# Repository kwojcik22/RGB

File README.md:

# RGB LED Controller Project

This repository contains hardware and firmware for an RGB LED controller based on the STM32F091 microcontroller. The project includes PCB design files, firmware source code, and documentation.

## Project Structure

- **pcb projects/**  
  KiCad PCB design files for the RGB LED controller hardware.
  - `RGBLED_v1/` – Main PCB project files and backups.
  - `doc/` – Additional PCB-related documentation.

- **firmware/W8/**  
  STM32CubeIDE firmware project for the STM32F091 MCU.
  - `Core/` – Main application source and header files.
  - `dimming/` – LED dimming logic.
  - `Drivers/` – HAL and CMSIS drivers.
  - `Debug/`, `Release/` – Build output directories.
  - `STM32F091RCTX_FLASH.ld` – Linker script.
  - `.ioc` – STM32CubeMX configuration file.

- **doc/**  
  Documentation and resources.
 
## Getting Started

### Requirements

- STM32CubeIDE (for firmware development)
- KiCad (for PCB design)
- ST-Link programmer/debugger
- STM32F091-based hardware

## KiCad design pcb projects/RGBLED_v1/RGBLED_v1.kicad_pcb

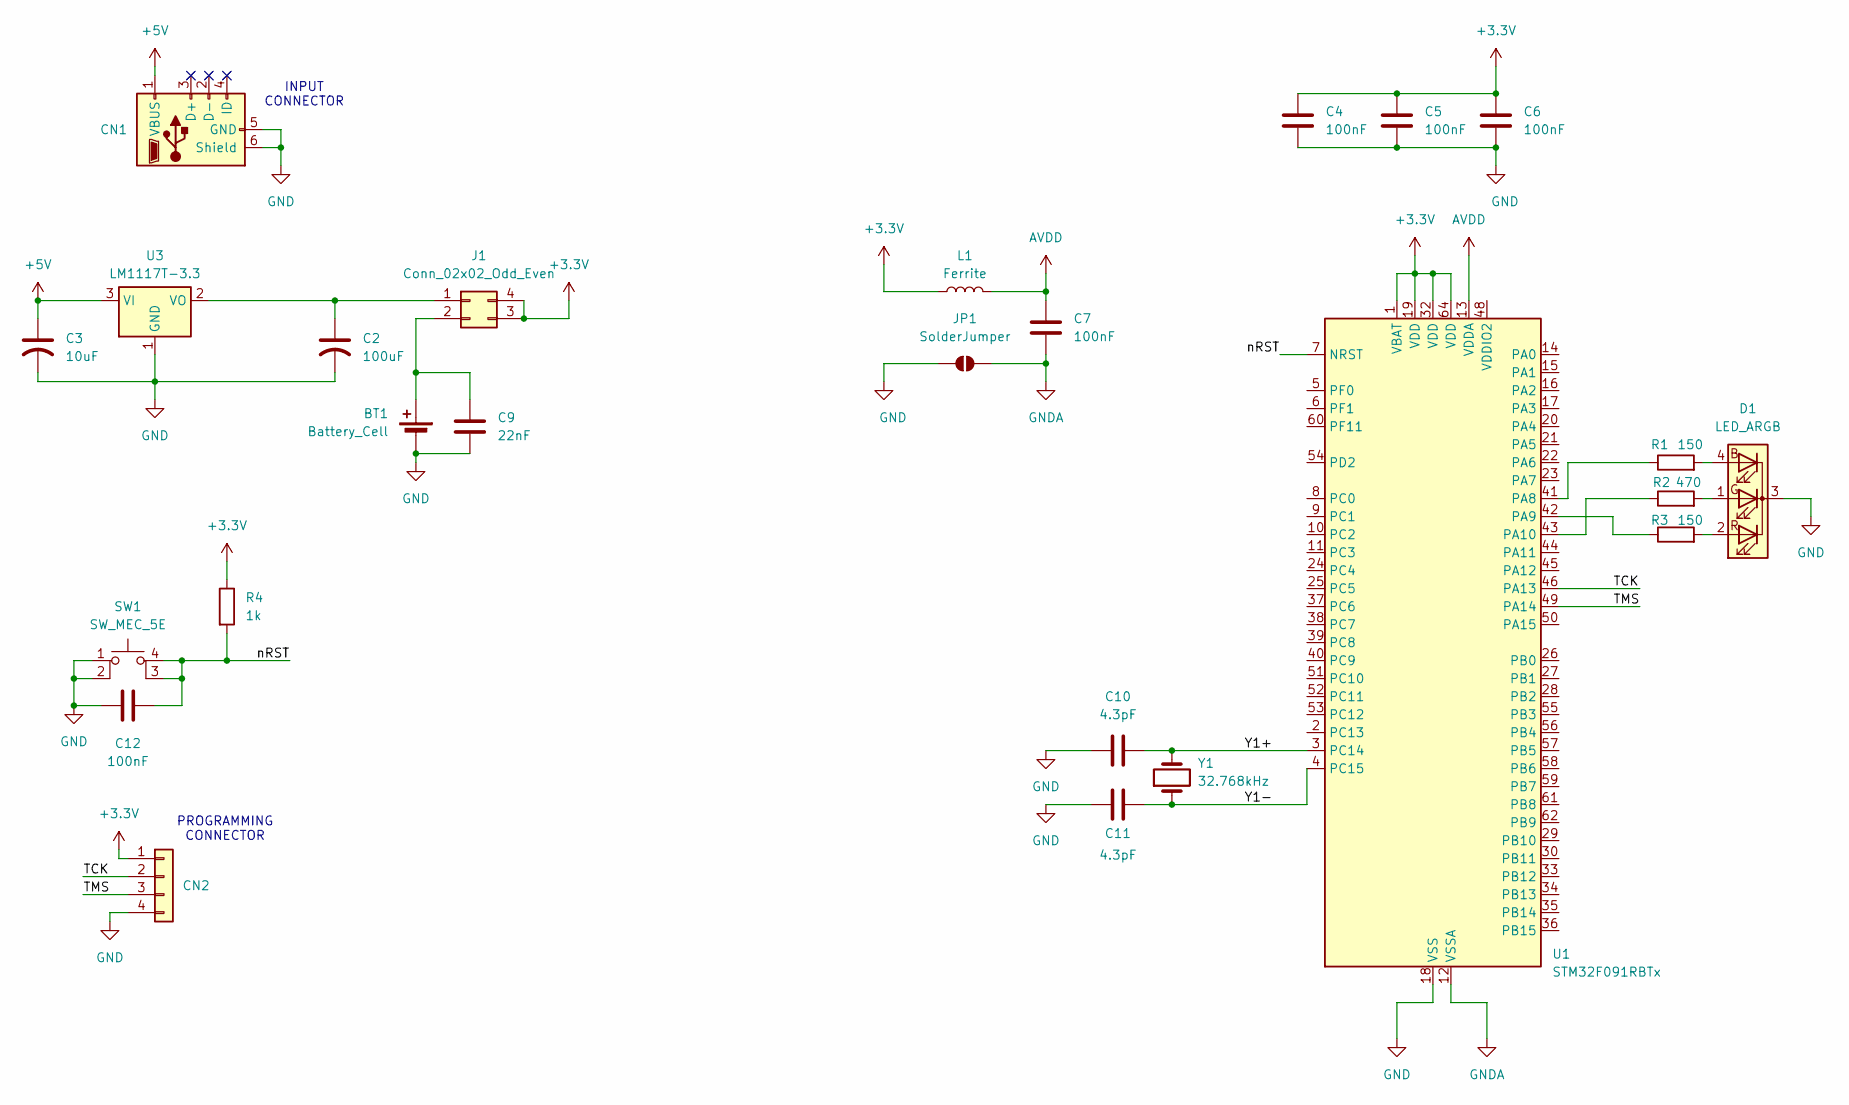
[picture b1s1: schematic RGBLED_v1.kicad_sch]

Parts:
BT1: Battery_Cell; BatteryHolder_MYOUNG_BS-07-A1BJ001_CR2032
C2: 100uF; CP_EIA-3528-21_Kemet-B_HandSolder
C3: 10uF; CP_EIA-3528-21_Kemet-B_HandSolder
C4, C5, C6, C7: 100nF; C_1206_3216Metric_Pad1.33x1.80mm_HandSolder
C9: 22nF; C_1206_3216Metric_Pad1.33x1.80mm_HandSolder
C10, C11: 4.3pF; C_1206_3216Metric_Pad1.33x1.80mm_HandSolder
C12: 100nF; CP_EIA-3528-21_Kemet-B_HandSolder
CN1: USB_B_Micro; USB_Micro-AB_Molex_47590-0001
CN2: Conn_01x03_Pin; PinHeader_1x04_P2.54mm_Vertical
D1: LED_ARGB; PinHeader_1x04_P2.54mm_Vertical
J1: Conn_02x02_Odd_Even; PinHeader_2x02_P2.54mm_Vertical
JP1: SolderJumper; SolderJumper-2_P1.3mm_Open_TrianglePad1.0x1.5mm
L1: Ferrite; L_0603_1608Metric_Pad1.05x0.95mm_HandSolder
R1, R3: 150; R_0805_2012Metric_Pad1.20x1.40mm_HandSolder
R2: 470; R_0805_2012Metric_Pad1.20x1.40mm_HandSolder
R4: 1k; R_0805_2012Metric_Pad1.20x1.40mm_HandSolder
SW1: SW_MEC_5E; SW_MEC_5GSH9
U1: STM32F091RBTx; LQFP-64_10x10mm_P0.5mm
U3: LM1117T-3.3; TO-220-3_Vertical
Y1: 32.768kHz; Crystal_SMD_HC49-SD_HandSoldering

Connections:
+3.3V: C4.2, C5.2, C6.2, CN2.1, J1.3, J1.4, L1.1, R4.1, U1.1 (VBAT), U1.19 (VDD), U1.32 (VDD), U1.64 (VDD)
+5V: C3.1, CN1.1 (VBUS), U3.3 (VI)
/TCK: CN2.2, U1.46 (PA13)
/TMS: CN2.3, U1.49 (PA14)
/Y1+: C10.2, U1.3 (PC14), Y1.2
/Y1-: C11.1, U1.4 (PC15), Y1.1
/nRST: C12.2, R4.2, SW1.3 (K), SW1.4 (A), U1.7 (NRST)
AVDD: C7.2, L1.2, U1.13 (VDDA)
GND: BT1.2 (-), C2.2, C3.2, C4.1, C5.1, C6.1, C9.2, C10.1, C11.2, C12.1, CN1.5 (GND), CN1.6 (Shield), CN2.4, D1.3 (GA), JP1.1 (A), SW1.1, SW1.2, U1.18 (VSS), U1.31 (VSS), U1.47 (VSS), U1.63 (VSS), U3.1 (GND)
GNDA: C7.1, JP1.2 (B), U1.12 (VSSA)
unnamed: BT1.1 (+), C9.1, J1.2
unnamed: D1.4 (BA), R1.2
unnamed: D1.1 (K), R2.2
unnamed: D1.2 (RA), R3.2
unnamed: C2.1, J1.1, U3.2 (VO)
unnamed: R1.1, U1.41 (PA8)
unnamed: R3.1, U1.42 (PA9)
unnamed: R2.1, U1.43 (PA10)

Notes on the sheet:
INPUT CONNECTOR
PROGRAMMING CONNECTOR

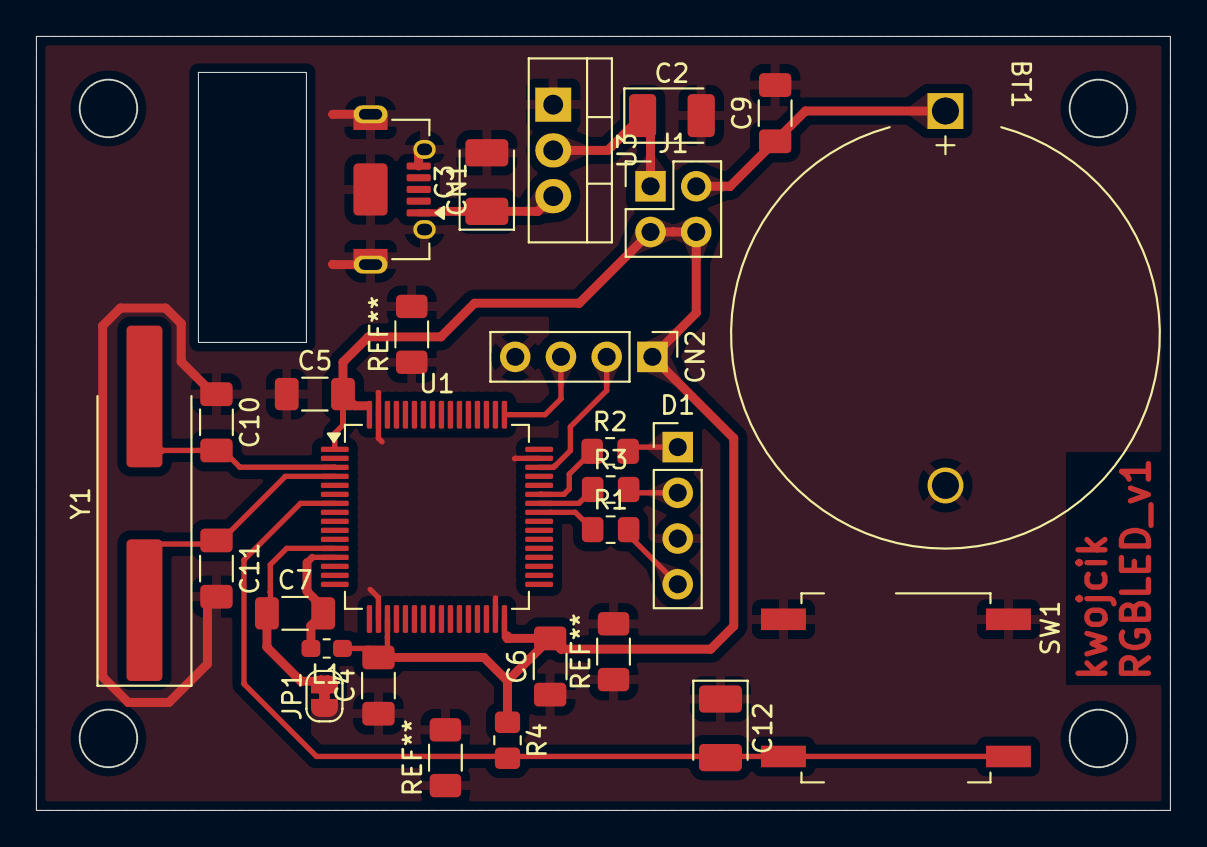
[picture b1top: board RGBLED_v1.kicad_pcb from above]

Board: 2 copper layers, 63.0 x 43.0 mm, 25 parts (0 on the bottom side), 18 nets.

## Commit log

2025-08-21 revert
2025-08-21 initial
2025-08-23 untrack settings
2025-08-24 changed switch, added swd jpg
2025-09-03 board drawing, footprints except slide switch
2025-09-22 nucleo docs
2025-09-22 mcu finished
2025-09-22 readme - project tree described
2025-10-01 components placement
2025-11-25 comp changes: stab to tht, cap to tantal; fixed comp placing on pcb
2025-11-25 digital signal net class added
2025-12-15 wired small traces, gnd polygon overwiev, no 3v3 trace
2025-12-16 traces done, GND plygon left
2025-12-17 removed buildin guide from readme
2025-12-19 diode fix added TODO.md
2025-12-28 D1 sch fix, stab fix, gnd zone fixed, started verification and BOM
2025-12-30 title added, D1 connected
2025-12-30 and jumper changed, hanging zones cut
2026-01-06 handcrafting pcb
2026-01-10 assigned elements
2026-03-16 grb pdf printed
